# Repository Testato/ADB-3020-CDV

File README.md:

# ADB-3020-CDV

The ADB-3020 is an excellent switching power supply designed by an Italian team and licensed under Creative Commons (the original project and credits are in the adb_2030_Original subfolder).

The CDV (Community Digital Version) fork is intended to start with version 2.1 (last published on the fork date) and then extend it with digital functions via MCU.
The project started with the creation of Eagle .sch because the original authors have decided not to release the productions files. 
Now Eagle file is deprecated, the project is ported on KiCAD.

The CDV version is released under the same license as the original project:
- https://creativecommons.org/licenses/by-nc-sa/4.0/

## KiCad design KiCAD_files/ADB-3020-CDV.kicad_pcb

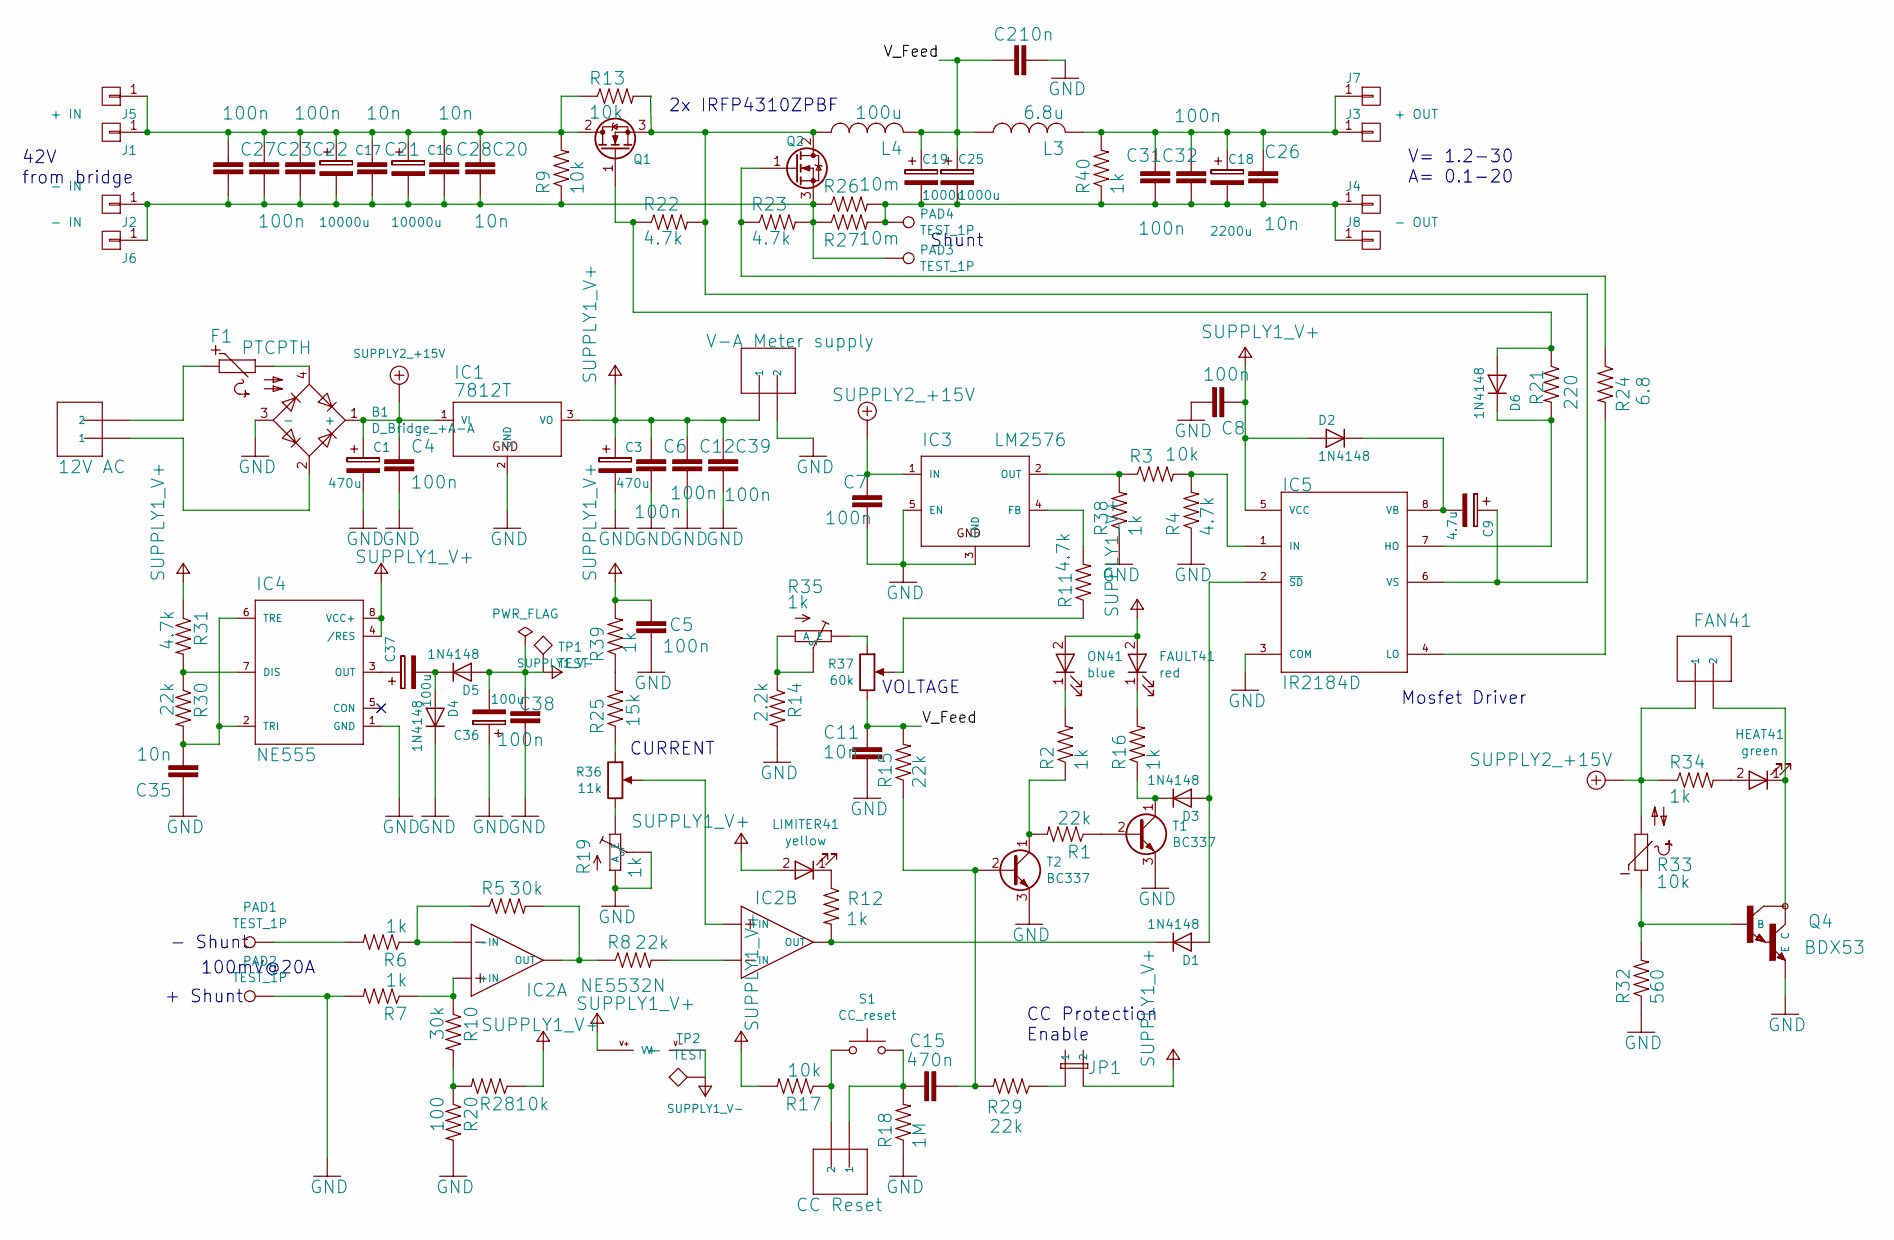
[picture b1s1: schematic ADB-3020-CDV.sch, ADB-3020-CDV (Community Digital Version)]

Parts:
B1: D_Bridge_+A-A; Diode_Bridge_Round_D9.8mm
C1, C3: 470u; CP_Radial_D10.0mm_P5.00mm
C2, C11, C35: 10n; C_0805
C4, C5, C6, C7, C8, C12, C38, C39: 100n; C_0805
C9: 4.7u; CP_Radial_D5.0mm_P2.00mm
C15: 470n; C_0805
C16, C17: 10000u; CP_Radial_D30.0mm_P10.00mm_SnapIn
C18: 2200u; CP_Radial_D18.0mm_P7.50mm
C19, C25: 1000u; CP_Radial_D16.0mm_P7.50mm
C20, C21, C26, C28: 10n; C_1206
C22, C23, C27, C31, C32: 100n; C_1206
C36, C37: 100u; CP_Radial_D6.3mm_P2.50mm
D1, D2, D3: 1N4148; D_DO-35_SOD27_P10.16mm_Horizontal
D4, D5: 1N4148; D_DO-35_SOD27_P7.62mm_Horizontal
D6: 1N4148; D_DO-35_SOD27_P12.70mm_Horizontal
F1: PTCPTH; R_Axial_DIN0204_L3.6mm_D1.6mm_P5.08mm_Horizontal
FAN41: fan; PhoenixContact_MCV-G_02x5.08mm_Vertical
FAULT41: red; LED_D3.0mm
HEAT41: green; LED_D3.0mm
IC1: 7812T; TO-220_Vertical
IC2: NE5532N; DIP-8_W7.62mm_LongPads
IC3: LM2576; TO-220-5_Pentawatt_Multiwatt-5_Vertical_StaggeredType1
IC4: NE555; DIP-8_W7.62mm_LongPads
IC5: IR2184D; DIP-8_W7.62mm_LongPads
J1, J5: + IN; faston_6.3mm
J2, J6: - IN; faston_6.3mm
J3, J7: + OUT; faston_6.3mm
J4, J8: - OUT; faston_6.3mm
JP1: jp1; Pin_Header_Straight_1x02_Pitch2.54mm
L3: 6.8u; smallinductor
L4: 100u; biginductor
LIMITER41: yellow; LED_D3.0mm
LOGIC_POWER41: 12V AC; PhoenixContact_MCV-G_02x5.08mm_Vertical
ON41: blue; LED_D3.0mm
PAD1, PAD2, PAD3, PAD4: TEST_1P; SolderWirePad_single_1mmDrill
Q1, Q2: IRFP4310ZPBF; TO-247_TO-3P_Horizontal
Q4: BDX53; TO-126_Vertical
R1, R8, R29, R30: 22k; R_Axial_DIN0204_L3.6mm_D1.6mm_P5.08mm_Horizontal
R2, R7, R12, R16, R34, R39: 1k; R_Axial_DIN0204_L3.6mm_D1.6mm_P5.08mm_Horizontal
R3: 10k; R_Axial_DIN0204_L3.6mm_D1.6mm_P7.62mm_Horizontal
R4, R11, R31: 4.7k; R_Axial_DIN0204_L3.6mm_D1.6mm_P5.08mm_Horizontal
R5, R10: 30k; R_Axial_DIN0204_L3.6mm_D1.6mm_P5.08mm_Horizontal
R6: 1k; R_Axial_DIN0204_L3.6mm_D1.6mm_P7.62mm_Horizontal
R9, R13: 10k; R_Axial_DIN0207_L6.3mm_D2.5mm_P10.16mm_Horizontal
R14: 2.2k; R_Axial_DIN0204_L3.6mm_D1.6mm_P5.08mm_Horizontal
R15: 22k; R_Axial_DIN0204_L3.6mm_D1.6mm_P7.62mm_Horizontal
R17, R28: 10k; R_Axial_DIN0204_L3.6mm_D1.6mm_P5.08mm_Horizontal
R18: 1M; R_Axial_DIN0204_L3.6mm_D1.6mm_P5.08mm_Horizontal
R19, R35: 1k; Potentiometer_Trimmer_Bourns_3296Y
R20: 100; R_Axial_DIN0204_L3.6mm_D1.6mm_P5.08mm_Horizontal
R21: 220; R_Axial_DIN0207_L6.3mm_D2.5mm_P15.24mm_Horizontal
R22, R23: 4.7k; R_Axial_DIN0207_L6.3mm_D2.5mm_P10.16mm_Horizontal
R24: 6.8; R_Axial_DIN0207_L6.3mm_D2.5mm_P15.24mm_Horizontal
R25: 15k; R_Axial_DIN0204_L3.6mm_D1.6mm_P5.08mm_Horizontal
R26, R27: 10m; R_2512
R32: 560; R_Axial_DIN0204_L3.6mm_D1.6mm_P5.08mm_Horizontal
R33: 10k; R_Axial_DIN0204_L3.6mm_D1.6mm_P2.54mm_Vertical
R36: 11k; Potentiometer_Trimmer_ACP_CA9v_Horizontal_Px10.0mm_Py5.0mm
R37: 60k; Potentiometer_Trimmer_ACP_CA9v_Horizontal_Px10.0mm_Py5.0mm
R38: 1k; R_Axial_DIN0207_L6.3mm_D2.5mm_P10.16mm_Horizontal
R40: 1k; R_Axial_DIN0309_L9.0mm_D3.2mm_P12.70mm_Horizontal
RESET41: CC Reset; Pin_Header_Straight_1x02_Pitch2.54mm
S1: CC_reset; SW_PUSH_6mm
T1, T2: BC337; TO-92_Molded_Narrow
TP1, TP2: TEST; SolderWirePad_single_1mmDrill
V-A_METER_SUPPLY41: V-A Meter supply; Pin_Header_Straight_1x02_Pitch2.54mm

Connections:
+15V: B1.1 (+), C1.1, C4.1, C7.1, FAN41.1, IC1.1 (VI), IC3.1 (IN), R33.2, R34.1
/V_Feed: C2.1, C11.1, C19.1, C25.1, L3.1, L4.2, R15.2, R37.3
GND: B1.3 (-), C1.2, C2.2, C3.2, C4.2, C5.1, C6.2, C7.2, C8.2, C11.2, C12.2, C35.1, C36.1, C38.1, C39.2, D4.1 (K), IC1.2 (GND), IC3.3 (GND), IC3.5 (EN), IC4.1 (GND), IC5.3 (COM), PAD2.1, Q4.3 (E), R4.1, R7.2, R14.2, R18.1, R19.1 (A), R19.2 (S), R20.2, R32.1, R38.1, T1.3 (E), T2.3 (E), V-A_METER_SUPPLY41.2
unnamed: B1.2, LOGIC_POWER41.1
unnamed: B1.4, F1.2
unnamed: C9.1, IC5.6 (VS), L4.1, Q1.3 (S), Q2.2 (D), R13.2, R22.2
unnamed: C9.2, D2.1 (K), IC5.8 (VB)
unnamed: C15.1, R18.2, RESET41.1, S1.2
unnamed: C15.2, R15.1, R29.2, T2.2 (B)
unnamed: C16.1, C17.1, C20.1, C21.1, C22.1, C23.1, C27.1, C28.1, J1.1, J5.1, Q1.2 (D), R9.2, R13.1
unnamed: C16.2, C17.2, C20.2, C21.2, C22.2, C23.2, C27.2, C28.2, J2.1, J6.1, PAD3.1, Q2.3 (S), R9.1, R23.2, R26.1, R27.1
unnamed: C18.1, C26.1, C31.1, C32.1, J3.1, J7.1, L3.2, R40.2
unnamed: C18.2, C19.2, C25.2, C26.2, C31.2, C32.2, J4.1, J8.1, PAD4.1, R26.2, R27.2, R40.1
unnamed: C35.2, IC4.2 (TRI), IC4.6 (TRE), R30.2
unnamed: C37.1, IC4.3 (OUT)
unnamed: C37.2, D4.2 (A), D5.1 (K)
unnamed: D1.1 (K), IC2.7 (OUT), R12.2
unnamed: D1.2 (A), D3.2 (A), IC5.2 (~SD)
unnamed: D3.1 (K), R16.1, T1.1 (C)
unnamed: D6.1 (K), IC5.7 (HO), R21.2
unnamed: D6.2 (A), Q1.1 (G), R21.1, R22.1
unnamed: F1.1, LOGIC_POWER41.2
unnamed: FAN41.2, HEAT41.1 (K), Q4.2 (C)
unnamed: FAULT41.1 (K), R16.2
unnamed: HEAT41.2 (A), R34.2
unnamed: IC2.1 (OUT), R5.2, R8.1
unnamed: IC2.2 (-IN), R5.1, R6.1
unnamed: IC2.3 (+IN), R7.1, R10.1
unnamed: IC2.5 (+IN), R36.2
unnamed: IC2.6 (-IN), R8.2
unnamed: IC3.2 (OUT), R3.1, R38.2
unnamed: IC3.4 (FB), R11.2
unnamed: IC4.7 (DIS), R30.1, R31.2
unnamed: IC5.1 (IN), R3.2, R4.2
unnamed: IC5.4 (LO), R24.2
unnamed: JP1.1, R29.1
unnamed: LIMITER41.1 (K), R12.1
unnamed: ON41.1 (K), R2.2
unnamed: PAD1.1, R6.2
unnamed: Q2.1 (G), R23.1, R24.1
unnamed: Q4.1 (B), R32.2, R33.1
unnamed: R1.1, T1.2 (B)
unnamed: R1.2, R2.1, T2.1 (C)
unnamed: R10.2, R20.1, R28.2
unnamed: R11.1, R37.2
unnamed: R14.1, R35.1 (A), R35.2 (S)
unnamed: R17.1, RESET41.2, S1.1
unnamed: R19.3 (E), R36.3
unnamed: R25.1, R36.1
unnamed: R25.2, R39.1
unnamed: R35.3 (E), R37.1
V+: C3.1, C5.2, C6.1, C8.1, C12.1, C39.1, D2.2 (A), FAULT41.2 (A), IC1.3 (VO), IC2.8 (V+), IC4.4 (/RES), IC4.8 (VCC+), IC5.5 (VCC), JP1.2, LIMITER41.2 (A), ON41.2 (A), R17.2, R28.1, R31.1, R39.2, V-A_METER_SUPPLY41.1
V-: C36.2, C38.2, D5.2 (A), IC2.4 (V-), TP1.1, TP2.1

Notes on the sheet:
2x IRFP4310ZPBF
100mV@20A
- Shunt
+ Shunt
~ Shunt
42V from bridge
V= 1.2-30 A= 0.1-20
CURRENT
VOLTAGE
CC Protection Enable
Mosfet Driver

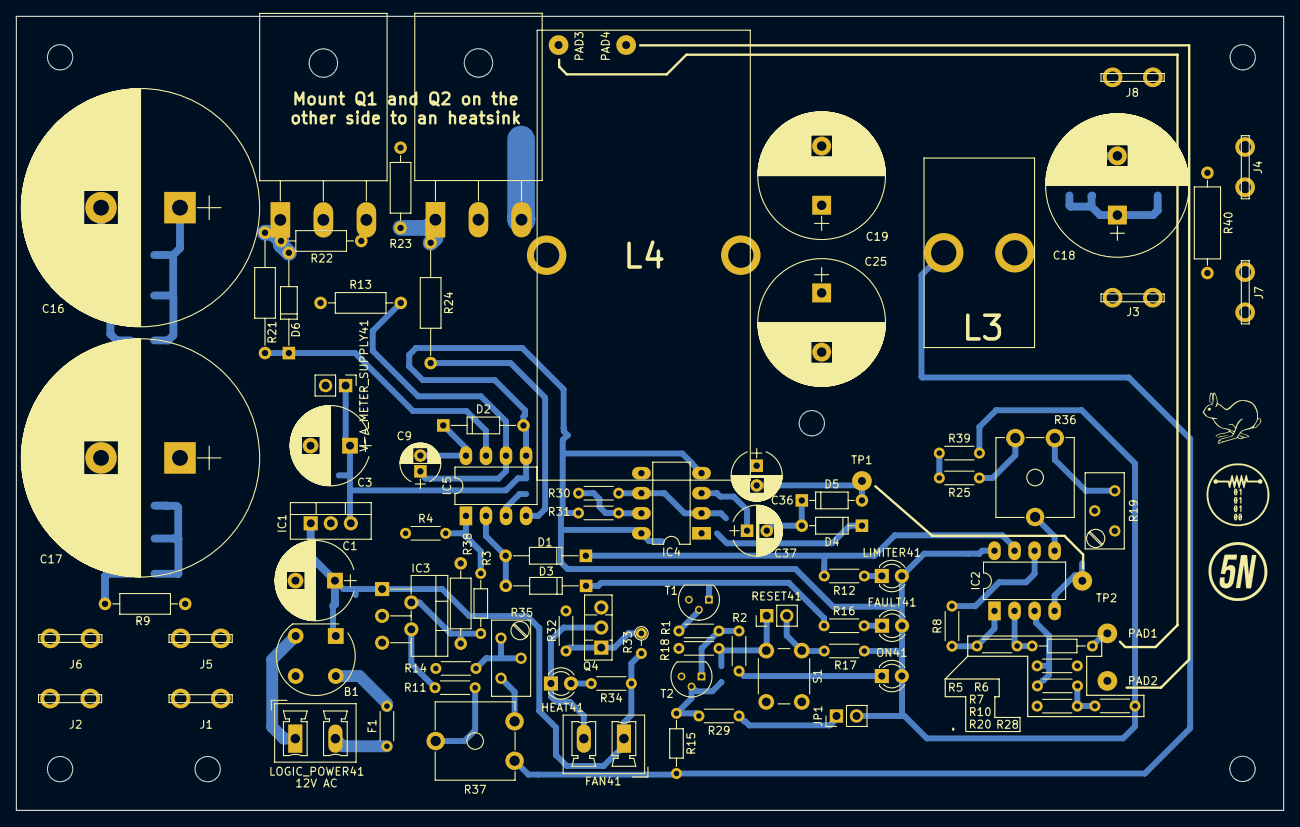
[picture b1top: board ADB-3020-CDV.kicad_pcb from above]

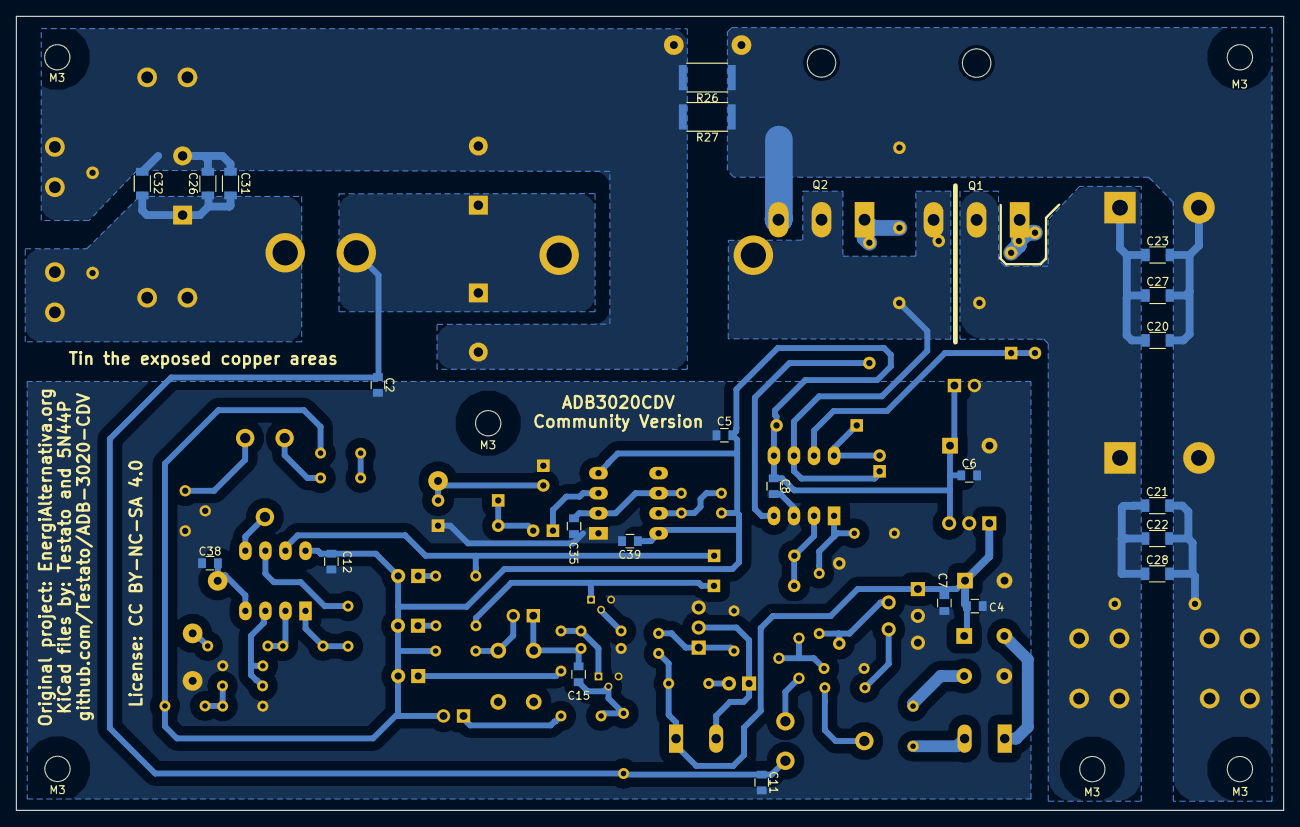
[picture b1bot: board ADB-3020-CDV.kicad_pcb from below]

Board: 2 copper layers, 160.5 x 100.6 mm, 121 parts (29 on the bottom side), 53 nets.

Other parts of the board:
M3, M3#2, M3#3, M3#4, M3#5, M3#6: MountingHole_3.2mm_M3

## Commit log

2017-05-27 Update README.md
    The license name was wrong (https://github.com/Testato/ADB-3020-CDV/issues/1)
2017-05-27 added ne5532 supply pins
2017-05-28 Complete boom included external components
2017-05-28 info added
2017-05-30 Added components values, reviewed some connections
    Waiting for a review before merge
2017-05-31 Fixed component designators
    Fixed components designators to match those in the original schematic and bom
2017-05-31 Fixed some connections
2017-06-02 Create LICENSE
2017-06-02 Rename LICENSE to LICENSE.md
2017-06-02 Grid 0,1" + some component name corrections
2017-06-03 removed unused joint connection + minor graphic change
2017-08-26 Added footprints
    To do before merge:
    * review the footprints
    * draw inductors footprints
    * draw J1 to J8 footprints (faston tabs)
2017-08-26 first KiCAD version whit sch and pcb
2017-08-27 Almost finished layout and fixes.
    * fixed fp-lib-table
    * fixed schematic
    Missing:
    * faston footprints
    * faston in layout
    Requires review
2017-08-29 Completed layout
    * added last footprints
    * added silkscreen wordings
    * adedd logos
    * added soldermask zones
    * fixed component identifier positions
    Missing:
2017-08-29 Completed the layout
2017-08-30 Removed all ERC, repaired annotation on sch and pcb, added sheet pcb info, revisited .sch component name value position
2018-01-30 Creato .gitattributes

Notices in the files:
KiCAD_files/ADB-3020-CDV.kicad_pcb:
License: CC BY-NC-SA 4.0
